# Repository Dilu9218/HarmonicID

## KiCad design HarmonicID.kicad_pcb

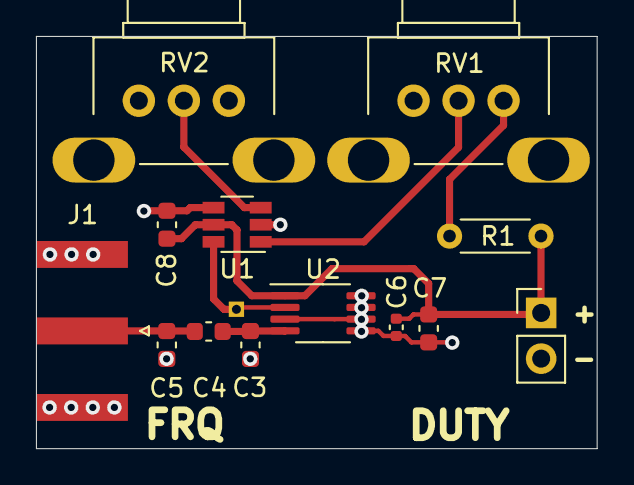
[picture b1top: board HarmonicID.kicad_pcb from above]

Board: 2 copper layers, 31.2 x 22.9 mm, 14 parts (0 on the bottom side), 8 nets.

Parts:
C3, C4, C5: C; C_0603_1608Metric
C6: 0.1uF; C_0402_1005Metric
C7: 1uF; C_0603_1608Metric
C8: 0.1u; C_0603_1608Metric
J1: Conn_Coaxial; SMA_Amphenol_132289_EdgeMount
J2: Conn_01x01_Female; PinHeader_1x01_P1.00mm_Vertical
P1: INPUT POWER; PinHeader_1x02_P2.54mm_Vertical
R1: 130K; R_Axial_DIN0204_L3.6mm_D1.6mm_P5.08mm_Horizontal
RV1, RV2: 100K; Potentiometer_Alps_RK09K_Single_Horizontal
U1: LTC6993xS6-1; TSOT-23-6
U2: ADG902BRMZ; MSOP-8_3x3mm_P0.65mm

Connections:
/RF1: C3.2, C4.2, U2.4
/RF1_: C4.1, C5.2, J1.1
CTRL: J2.1, U1.6, U2.2
GND: C3.1, C5.1, C6.2, C7.2, C8.1, J1.2, P1.2, RV1.3, RV2.3, U1.2, U1.4, U2.3, U2.5, U2.6, U2.7, U2.8
unnamed: R1.1, RV1.1
unnamed: RV1.2, U1.1
unnamed: RV2.2, U1.3
VDD: C6.1, C7.1, C8.2, P1.1, R1.2, U1.5, U2.1

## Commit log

2022-06-03 init
